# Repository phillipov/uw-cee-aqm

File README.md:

# uw-cee-aqm
Files for designing an air quality monitoring sensor for the UW Seattle CEE department.

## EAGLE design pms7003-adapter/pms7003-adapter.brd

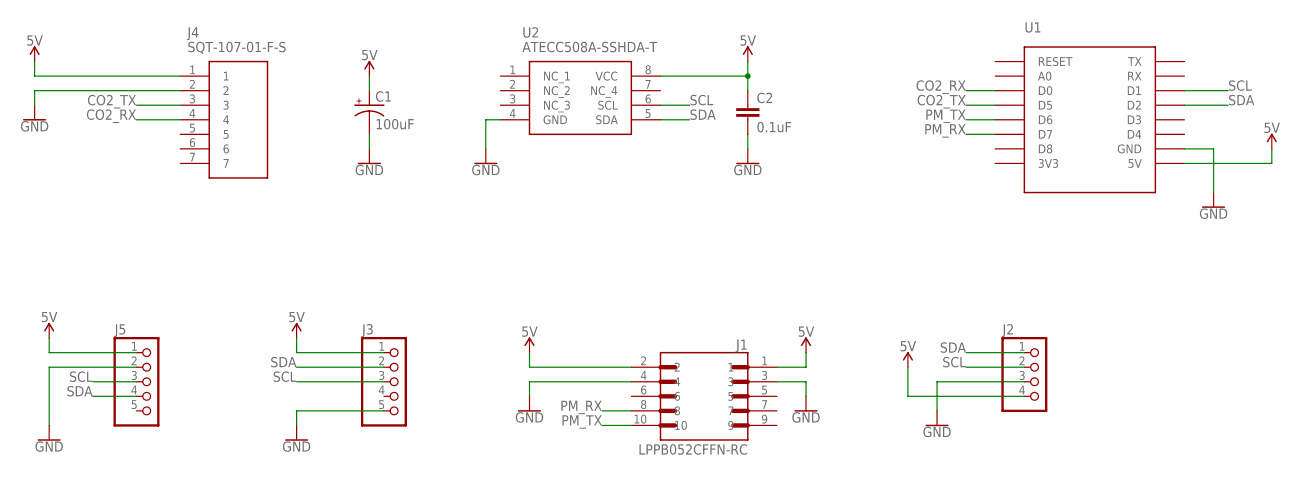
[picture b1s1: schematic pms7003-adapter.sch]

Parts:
C1: 100uF; CPOL-RADIAL-2.5MM-6.5MM
C2: 0.1uF; 0603
J1: LPPB052CFFN-RC; SULLINS_LPPB052CFFN-RC
J2: PINHD-1X4; 1X04
J3, J5: PINHD-1X5; 1X05
J4: SQT-107-01-F-S; SQT-107-01-XX-S
U1: WEMOS-D1-MINI
U2: ATECC508A-SSHDA-T; SOIC127P600X175-8N

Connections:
5V: C1.1 (+), C2.1, J1.1, J1.2, J2.4, J3.1, J4.1, J5.1, U1.5V, U2.8 (VCC)
CO2_RX: J4.4, U1.D0
CO2_TX: J4.3, U1.D5
GND: C1.2 (-), C2.2, J1.3, J1.4, J2.3, J3.5, J4.2, J5.2, U1.GND, U2.4 (GND)
PM_RX: J1.8, U1.D7
PM_TX: J1.10, U1.D6
SCL: J2.2, J3.3, J5.3, U1.D1, U2.6 (SCL)
SDA: J2.1, J3.2, J5.4, U1.D2, U2.5 (SDA)

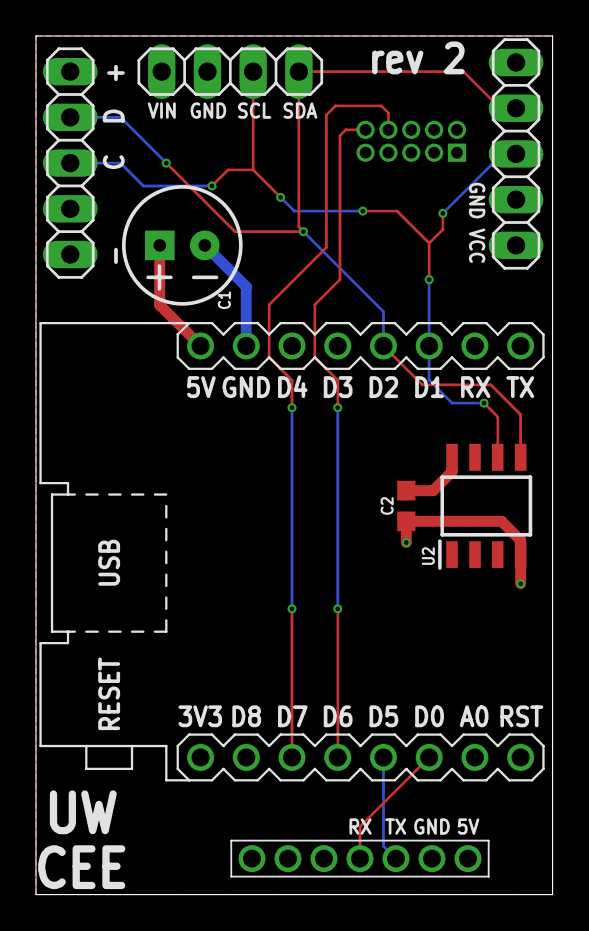
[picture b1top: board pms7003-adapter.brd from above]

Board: 2 copper layers, 28.7 x 47.7 mm, 9 parts (1 on the bottom side), 8 nets.

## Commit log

2020-03-30 PMS7003 adapter PCB is fabrication ready; started the laser cut DXF file
2020-03-31 Added NodeMCU to laser cut design files
2020-04-16 Added a DXF model for the PMS7003 and its zip tie holes
2020-04-16 Drew Pi cover outline, fixed hole laser outline in the Pi 4B drawing
2020-04-17 Added BME280 DXF, added marking layer to every part drawing
2020-04-21 Updated board markings, started adding parts to main drawing
2020-04-21 DXF layout complete for the Pi board rev0
2020-04-22 Reduced size of the PMS7003 adapter, replaced THT header with SMD header
2020-04-23 Smaller PMS7003 adapter is ready for fab
2020-04-24 created a production DXF file to stage exports to Ponoko
2020-05-03 Started integrating WiFi into the PMS adapter board
2020-05-09 Returned to modular design, no cables needed
2020-05-11 Optimized design size with D1 Mini
2020-05-12 Added silkscreen text. Fab ready!
2020-05-13 Refactored for CO2 sensor and different UART pins
2020-06-17 Added sensor Arduino sketch and data collector python script
2020-06-18 Now records to sqlite3 database file.
2020-06-19 Started code for OTA updates
2020-06-19 OTA updates work now.
2020-06-20 Data collector no longer outputs for every new data message
2020-06-24 0.0.2 sensor will reconnect to MQTT broker, added start/stop scripts
2020-06-25 Resized CO2 sensor connector, ripped up all traces for redesign
2020-06-28 Added an improved D1 mini footprint
2020-06-29 rev 2 board ready for fab!
2020-06-29 Added silkscreen pin names to light sensor connector
2020-09-10 rev3 hardware support, improved OTA update handling

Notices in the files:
parts and their libraries:
SparkFun-Capacitors: Licensing: Creative Commons ShareAlike 4.0 International - https://creativecommons.org/licenses/by-sa/4.0
